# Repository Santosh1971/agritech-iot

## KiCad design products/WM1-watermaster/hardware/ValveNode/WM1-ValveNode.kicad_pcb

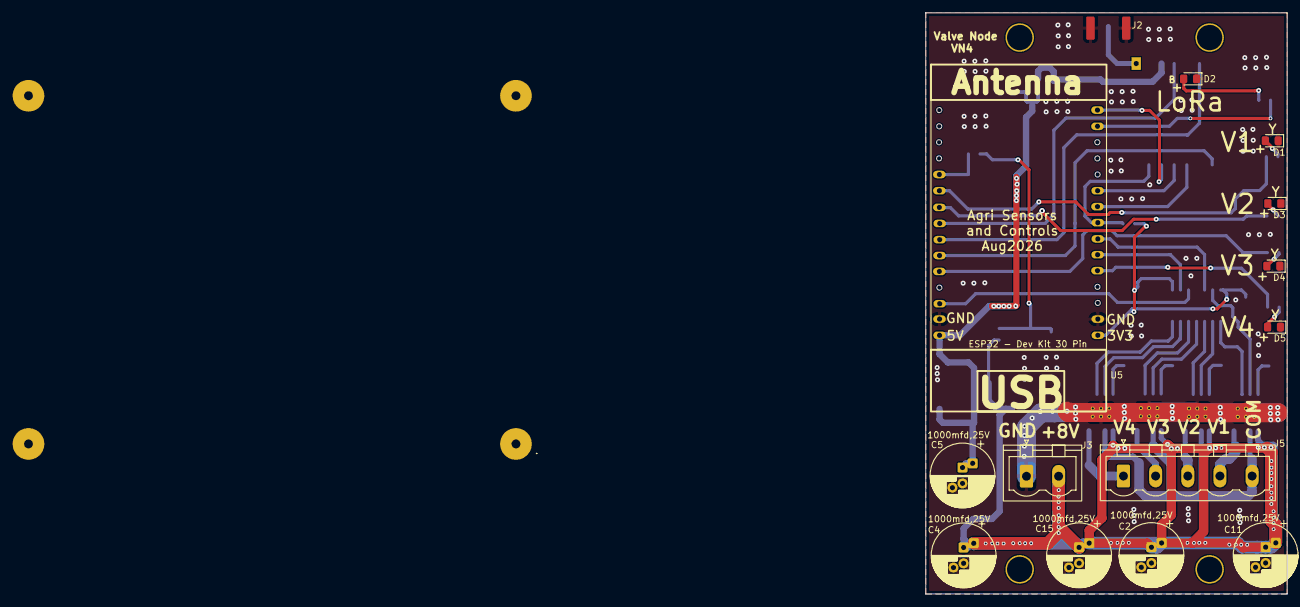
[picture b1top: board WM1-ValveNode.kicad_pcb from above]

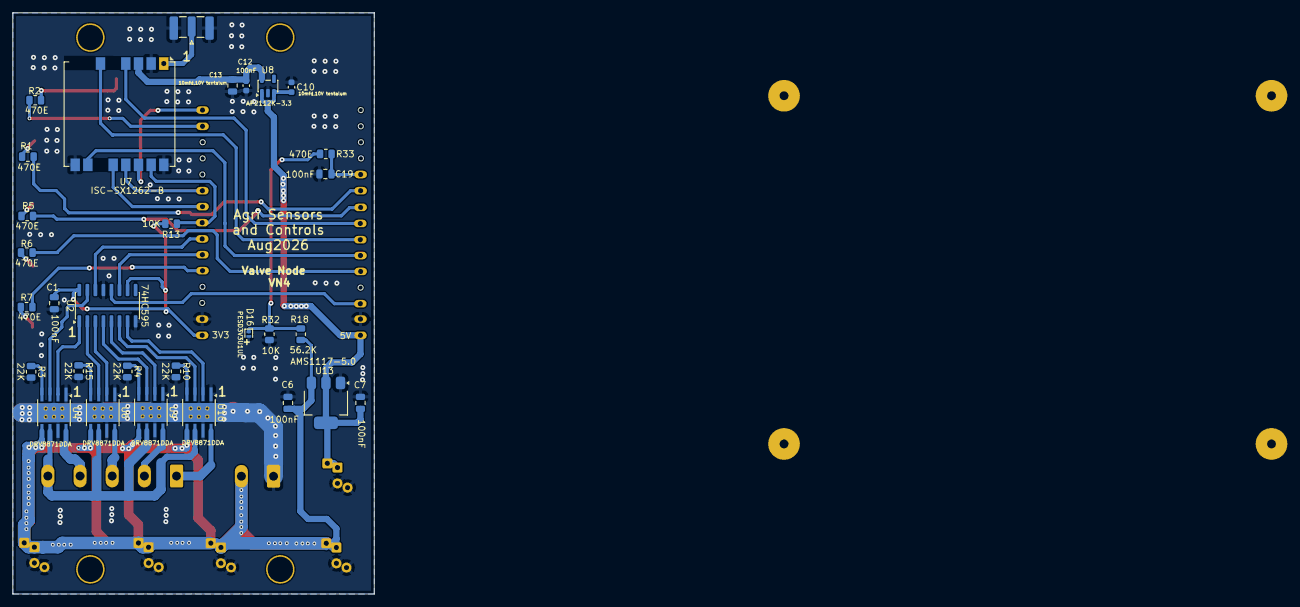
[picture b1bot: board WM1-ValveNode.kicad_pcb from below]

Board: 2 copper layers, 57.1 x 91.8 mm, 45 parts (30 on the bottom side), 45 nets.

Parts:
.: MountingHole; MountingHole_3.2mm_M3
C1, C6, C7, C13, C19: 100nF; C_0805_2012Metric
C2, C4, C5, C11, C15: 1000mfd,25V; CP_Radial_D10.0mm_P2.50mm_P5.00mm
C10, C12: 10mfd,10V tentalum; C_0603_1608Metric
D1: LED_V1_Yellow; LED_0805_2012Metric_Pad1.15x1.40mm_HandSolder
D2: LED_Blue_LoRa; LED_0805_2012Metric_Pad1.15x1.40mm_HandSolder
D3: LED_V2_Yellow; LED_0805_2012Metric_Pad1.15x1.40mm_HandSolder
D4: LED_V3_Yellow; LED_0805_2012Metric_Pad1.15x1.40mm_HandSolder
D5: LED_V4_Yellow; LED_0805_2012Metric_Pad1.15x1.40mm_HandSolder
D16: PESD3V3U1UL; D_SOD-882
H1: MountingHole; MountingHole_3.2mm_M3
J2: Conn_Coaxial_Small; SMA_Samtec_SMA-J-P-H-ST-EM1_EdgeMount
J3: PWR_CONN; PhoenixContact_MSTBVA_2,5_2-G-5,08_1x02_P5.08mm_Vertical
J5: Conn_01x05_Pin; PhoenixContact_MSTBVA_2,5_5-G-5,08_1x05_P5.08mm_Vertical
R1, R2, R5, R6, R7, R33: 470E; R_0805_2012Metric
R3, R4, R10, R15: 22K; R_0805_2012Metric
R13, R32: 10K; R_0805_2012Metric
R18: 56.2K; R_0805_2012Metric
U2: 74HC595; SOIC-16_3.9x9.9mm_P1.27mm
U4, U6, U9, U10: DRV8871DDA; Texas_HTSOP-8-1EP_3.9x4.9mm_P1.27mm_EP2.95x4.9mm_Mask2.4x3.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
U5: ESP32 30 Pin CP2102 Development Board; ESP32-C3-DevKitM-1
U7: ISC-SX1262-B; Ai-Thinker-Ra-01-LoRa
U8: AP2112K-3.3; SOT-23-5
U13: AMS1117-5.0; SOT-223-3_TabPin2

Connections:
+3.3V: C1.1, R13.1, U2.10 (~SRCLR), U2.16 (VCC), U5.1 (3V3_Out)
+3.3VL: C12.1, C13.1, U7.3 (VDD), U8.5 (VOUT)
+5V: C5.1, C7.1, C10.1, U5.30 (VIN/5V_Power_IN), U8.1 (VIN), U8.3 (EN), U13.2 (VO)
+8V: C2.1, C4.1, C6.1, C11.1, C15.1, J3.2, R18.1, U4.5 (VM), U6.5 (VM), U9.5 (VM), U10.5 (VM), U13.3 (VI)
/BUSY: U5.25 (D27), U7.10 (DIO4/BUSY)
/Batt_Mon: C19.1, R33.1, U5.20 (D35/Input_only)
/DIO1: U5.24 (D26), U7.6 (DIO1)
/LoRa_LED: R2.1, U5.14 (D22/I2C_SCL)
/MISO: U5.10 (D19), U7.13 (MISO)
/MOSI: U5.15 (D23), U7.14 (MOSI)
/NSS: R13.2, U5.8 (D5/BootSensitive), U7.15 (~NSS)
/RESET: U5.23 (D25), U7.4 (~RESET)
/SCK: U5.9 (D18), U7.12 (SCK)
/V1_IN1: U2.15 (QA), U4.3 (IN1)
/V1_IN2: U2.1 (QB), U4.2 (IN2)
/V1_LED: R1.1, U5.21 (D32)
/V1_OUT: J5.4, U4.8 (OUT2)
/V2_IN1: U2.2 (QC), U6.3 (IN1)
/V2_IN2: U2.3 (QD), U6.2 (IN2)
/V2_LED: R5.1, U5.22 (D33)
/V2_OUT: J5.3, U6.8 (OUT2)
/V3_IN1: U2.4 (QE), U9.3 (IN1)
/V3_IN2: U2.5 (QF), U9.2 (IN2)
/V3_LED: R6.1, U5.26 (D14)
/V3_OUT: J5.2, U9.8 (OUT2)
/V4_IN1: U2.6 (QG), U10.3 (IN1)
/V4_IN2: U2.7 (QH), U10.2 (IN2)
/V4_LED: R7.1, U5.5 (D4)
/V4_OUT: J5.1, U10.8 (OUT2)
/V_Com_OUT: J5.5, U4.6 (OUT1), U6.6 (OUT1), U9.6 (OUT1), U10.6 (OUT1)
/Valve_CLK: U2.11 (SRCLK), U5.6 (Rx2/D16)
/Valve_DATA: U2.14 (SER), U5.7 (Tx2/D17)
/Valve_LATCH: U2.12 (RCLK), U5.28 (D13)
GND: C1.2, C2.2, C4.2, C5.2, C6.2, C7.2, C10.2, C11.2, C12.2, C13.2, C15.2, C19.2, D1.1 (K), D2.1 (K), D3.1 (K), D4.1 (K), D5.1 (K), D16.2 (A), J2.2 (Ext), J3.1, R3.2, R4.2, R10.2, R15.2, R32.2, U2.8 (GND), U2.13 (~OE), U4.1 (GND), U4.7 (GND), U4.9 (GND), U5.2 (GND), U5.29 (GND), U6.1 (GND), U6.7 (GND), U6.9 (GND), U7.2 (GND), U7.9 (GND), U7.16 (GND), U8.2 (GND), U9.1 (GND), U9.7 (GND), U9.9 (GND), U10.1 (GND), U10.7 (GND), U10.9 (GND), U13.1 (GND)
unnamed: D1.2 (A), R1.2
unnamed: D2.2 (A), R2.2
unnamed: D3.2 (A), R5.2
unnamed: D4.2 (A), R6.2
unnamed: D5.2 (A), R7.2
unnamed: D16.1 (K), R18.2, R32.1, R33.2
unnamed: J2.1 (In), U7.1 (ANT)
unnamed: R3.1, U4.4 (ILIM)
unnamed: R15.1, U6.4 (ILIM)
unnamed: R4.1, U9.4 (ILIM)
unnamed: R10.1, U10.4 (ILIM)

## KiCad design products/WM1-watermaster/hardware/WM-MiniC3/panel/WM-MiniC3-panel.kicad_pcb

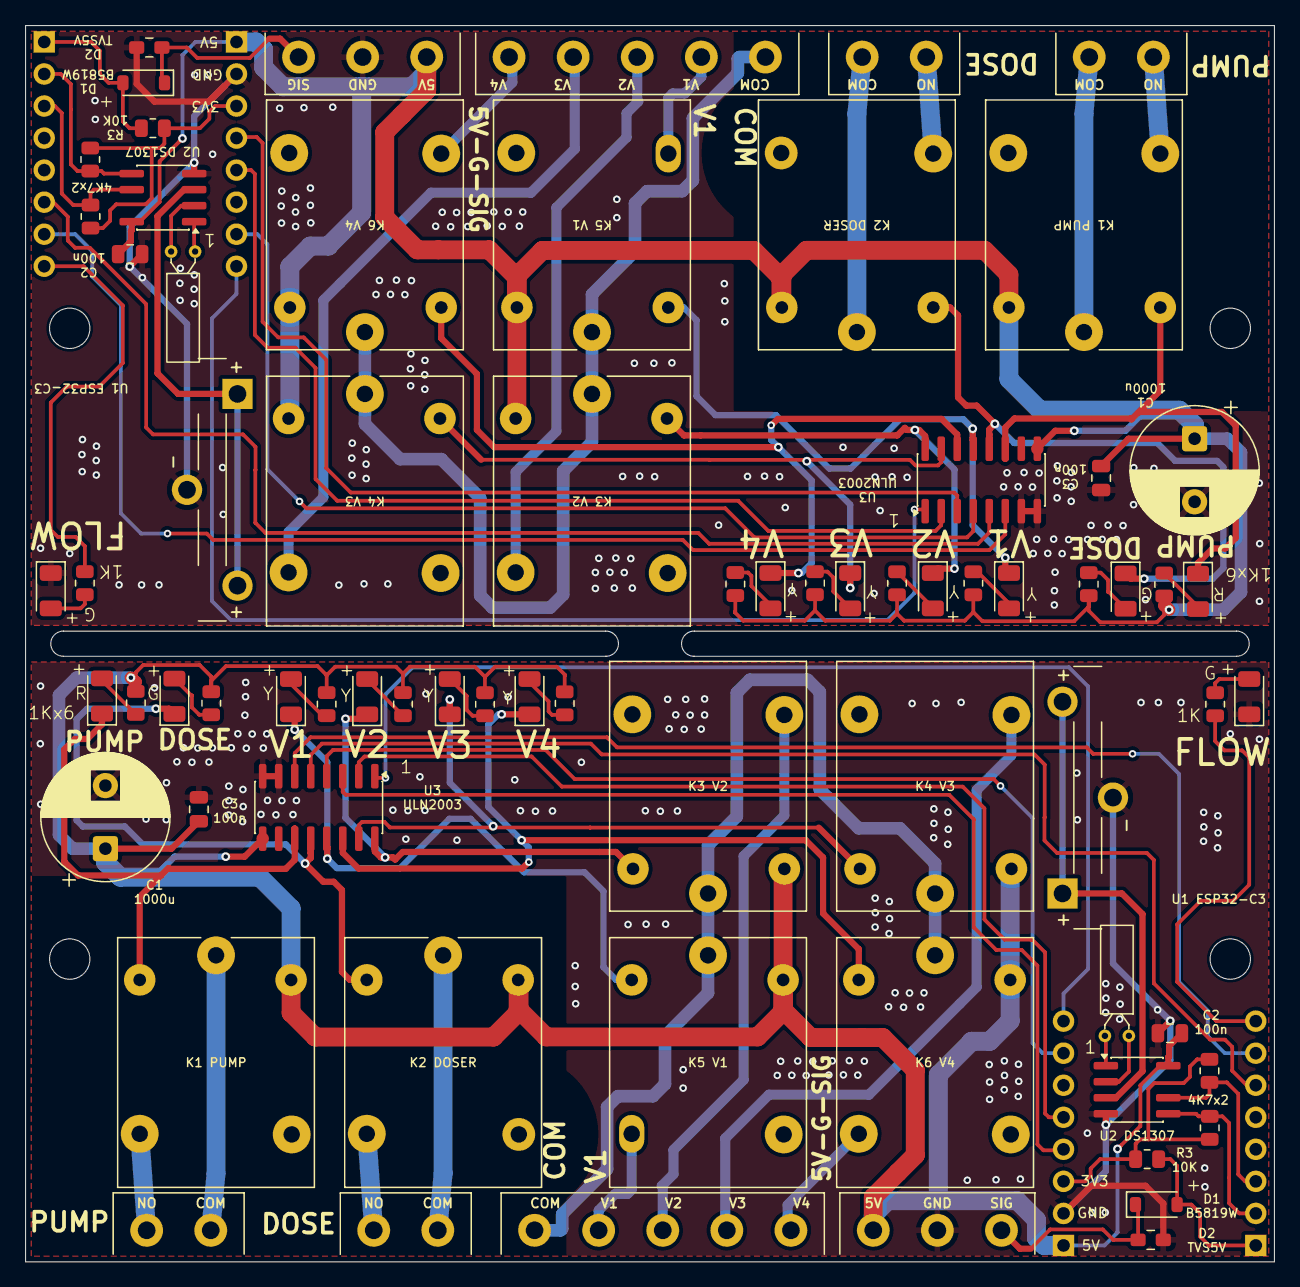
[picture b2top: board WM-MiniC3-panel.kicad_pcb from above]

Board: 2 copper layers, 99.0 x 98.0 mm, 78 parts (0 on the bottom side), 78 nets.

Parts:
BT1_1, BT1_2: CR2032; Battery_CR2032_Vertical_3pin
C1_1, C1_2: 1000u 16V; CP_Radial_D10.0mm_P5.00mm
C2_1, C2_2, C3_1, C3_2: 100n; C_0805_2012Metric
D1_1, D1_2: B5819W; D_SOD-123
D2_1, D2_2: SLCESDB5V0D5; D_SOD-523_HandSolder
D3_1, D3_2: GRN; LED_1206_3216Metric
D4_1, D4_2, D5_1, D5_2, D6_1, D6_2, D7_1, D7_2, D8_1, D8_2, D9_1, D9_2: YEL; LED_1206_3216Metric
H1_1, H1_2, H2_1, H2_2: M3; MountingHole_3.2mm_M3
J1_1, J1_2: FLOW; Pluggable_2EDGR_5.08_1x03_Horizontal
J2_1, J2_2: PUMP 230V; Pluggable_2EDGR_5.08_1x02_Horizontal
J3_1, J3_2: DOSER 230V; Pluggable_2EDGR_5.08_1x02_Horizontal
J4_1, J4_2: VALVES 24VAC; Pluggable_2EDGR_5.08_1x05_Horizontal
K1_1, K1_2, K2_1, K2_2, K3_1, K3_2, K4_1, K4_2, K5_1, K5_2, K6_1, K6_2: SRD-05VDC; Relay_SPDT_SANYOU_SRD_Outline
R1_1, R1_2, R2_1, R2_2: 4.7k; R_0805_2012Metric
R3_1, R3_2: 10k; R_0805_2012Metric
R4_1, R4_2, R6_1, R6_2, R7_1, R7_2, R8_1, R8_2, R9_1, R9_2, R10_1, R10_2, R11_1, R11_2: 1k; R_0805_2012Metric
U1_1, U1_2: ESP32-C3 Super Mini; ESP32-C3_SuperMini_Socket
U2_1, U2_2: DS1307Z+; SOIC-8_3.9x4.9mm_P1.27mm
U3_1, U3_2: ULN2003A; SOIC-16_3.9x9.9mm_P1.27mm
Y1_1, Y1_2: 32.768k; Crystal_C26-LF_D2.1mm_L6.5mm_Horizontal

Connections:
B1/+3V3: R1_1.1, R2_1.1, R3_1.1, U1_1.11 (3V3)
B1/+5V: C1_1.1, C2_1.1, C3_1.1, J1_1.1, K1_1.5, K2_1.5, K3_1.2, K4_1.2, K5_1.5, K6_1.5, R6_1.1, R7_1.1, R8_1.1, R9_1.1, R10_1.1, R11_1.1, U1_1.9 (5V), U2_1.8 (VCC), U3_1.9 (COM)
B1/COIL_DOSER: D4_1.1 (K), K2_1.2, U3_1.12 (O5)
B1/COIL_PUMP: D5_1.1 (K), K1_1.2, U3_1.11 (O6)
B1/COIL_V1: D6_1.1 (K), K5_1.2, U3_1.13 (O4)
B1/COIL_V2: D7_1.1 (K), K3_1.5, U3_1.16 (O1)
B1/COIL_V3: D8_1.1 (K), K4_1.5, U3_1.15 (O2)
B1/COIL_V4: D9_1.1 (K), K6_1.2, U3_1.14 (O3)
B1/DOSER_COM: J3_1.2, K2_1.1
B1/DOSER_NO: J3_1.1, K2_1.3
B1/FLOW: D1_1.2 (A), R3_1.2, U1_1.1 (IO5)
B1/FLOW_EXT: D1_1.1 (K), D2_1.1 (A1), J1_1.3
B1/GND: BT1_1.2 (-), C1_1.2, C2_1.2, C3_1.2, D2_1.2 (A2), D3_1.1 (K), J1_1.2, U1_1.10 (GND), U2_1.4 (GND), U3_1.7 (I7), U3_1.8 (GND)
B1/LED_FLOW: R4_1.1, U1_1.8 (IO21)
B1/Net-(D3-A): D3_1.2 (A), R4_1.2
B1/Net-(D4-A): D4_1.2 (A), R6_1.2
B1/Net-(D5-A): D5_1.2 (A), R7_1.2
B1/Net-(D6-A): D6_1.2 (A), R8_1.2
B1/Net-(D7-A): D7_1.2 (A), R9_1.2
B1/Net-(D8-A): D8_1.2 (A), R10_1.2
B1/Net-(D9-A): D9_1.2 (A), R11_1.2
B1/PUMP_COM: J2_1.2, K1_1.1
B1/PUMP_NO: J2_1.1, K1_1.3
B1/RLY_DOSER: U1_1.6 (IO10), U3_1.5 (I5)
B1/RLY_PUMP: U1_1.7 (IO20), U3_1.6 (I6)
B1/RLY_V1: U1_1.15 (IO1), U3_1.4 (I4)
B1/RLY_V2: U1_1.16 (IO0), U3_1.1 (I1)
B1/RLY_V3: U1_1.13 (IO3), U3_1.2 (I2)
B1/RLY_V4: U1_1.12 (IO4), U3_1.3 (I3)
B1/SCL: R2_1.2, U1_1.3 (IO7), U2_1.6 (SCL)
B1/SDA: R1_1.2, U1_1.2 (IO6), U2_1.5 (SDA)
B1/V1_NO: J4_1.2, K5_1.3
B1/V2_NO: J4_1.3, K3_1.3
B1/V3_NO: J4_1.4, K4_1.3
B1/V4_NO: J4_1.5, K6_1.3
B1/VALVE_COM: J4_1.1, K3_1.1, K4_1.1, K5_1.1, K6_1.1
B1/VBAT: BT1_1.1 (+), U2_1.3 (VBAT)
B1/XT1: U2_1.1 (X1), Y1_1.2
B1/XT2: U2_1.2 (X2), Y1_1.1
B2/+3V3: R1_2.1, R2_2.1, R3_2.1, U1_2.11 (3V3)
B2/+5V: C1_2.1, C2_2.1, C3_2.1, J1_2.1, K1_2.5, K2_2.5, K3_2.2, K4_2.2, K5_2.5, K6_2.5, R6_2.1, R7_2.1, R8_2.1, R9_2.1, R10_2.1, R11_2.1, U1_2.9 (5V), U2_2.8 (VCC), U3_2.9 (COM)
B2/COIL_DOSER: D4_2.1 (K), K2_2.2, U3_2.12 (O5)
B2/COIL_PUMP: D5_2.1 (K), K1_2.2, U3_2.11 (O6)
B2/COIL_V1: D6_2.1 (K), K5_2.2, U3_2.13 (O4)
B2/COIL_V2: D7_2.1 (K), K3_2.5, U3_2.16 (O1)
B2/COIL_V3: D8_2.1 (K), K4_2.5, U3_2.15 (O2)
B2/COIL_V4: D9_2.1 (K), K6_2.2, U3_2.14 (O3)
B2/DOSER_COM: J3_2.2, K2_2.1
B2/DOSER_NO: J3_2.1, K2_2.3
B2/FLOW: D1_2.2 (A), R3_2.2, U1_2.1 (IO5)
B2/FLOW_EXT: D1_2.1 (K), D2_2.1 (A1), J1_2.3
B2/GND: BT1_2.2 (-), C1_2.2, C2_2.2, C3_2.2, D2_2.2 (A2), D3_2.1 (K), J1_2.2, U1_2.10 (GND), U2_2.4 (GND), U3_2.7 (I7), U3_2.8 (GND)
B2/LED_FLOW: R4_2.1, U1_2.8 (IO21)
B2/Net-(D3-A): D3_2.2 (A), R4_2.2
B2/Net-(D4-A): D4_2.2 (A), R6_2.2
B2/Net-(D5-A): D5_2.2 (A), R7_2.2
B2/Net-(D6-A): D6_2.2 (A), R8_2.2
B2/Net-(D7-A): D7_2.2 (A), R9_2.2
B2/Net-(D8-A): D8_2.2 (A), R10_2.2
B2/Net-(D9-A): D9_2.2 (A), R11_2.2
B2/PUMP_COM: J2_2.2, K1_2.1
B2/PUMP_NO: J2_2.1, K1_2.3
B2/RLY_DOSER: U1_2.6 (IO10), U3_2.5 (I5)
B2/RLY_PUMP: U1_2.7 (IO20), U3_2.6 (I6)
B2/RLY_V1: U1_2.15 (IO1), U3_2.4 (I4)
B2/RLY_V2: U1_2.16 (IO0), U3_2.1 (I1)
B2/RLY_V3: U1_2.13 (IO3), U3_2.2 (I2)
B2/RLY_V4: U1_2.12 (IO4), U3_2.3 (I3)
B2/SCL: R2_2.2, U1_2.3 (IO7), U2_2.6 (SCL)
B2/SDA: R1_2.2, U1_2.2 (IO6), U2_2.5 (SDA)
B2/V1_NO: J4_2.2, K5_2.3
B2/V2_NO: J4_2.3, K3_2.3
B2/V3_NO: J4_2.4, K4_2.3
B2/V4_NO: J4_2.5, K6_2.3
B2/VALVE_COM: J4_2.1, K3_2.1, K4_2.1, K5_2.1, K6_2.1
B2/VBAT: BT1_2.1 (+), U2_2.3 (VBAT)
B2/XT1: U2_2.1 (X1), Y1_2.2
B2/XT2: U2_2.2 (X2), Y1_2.1

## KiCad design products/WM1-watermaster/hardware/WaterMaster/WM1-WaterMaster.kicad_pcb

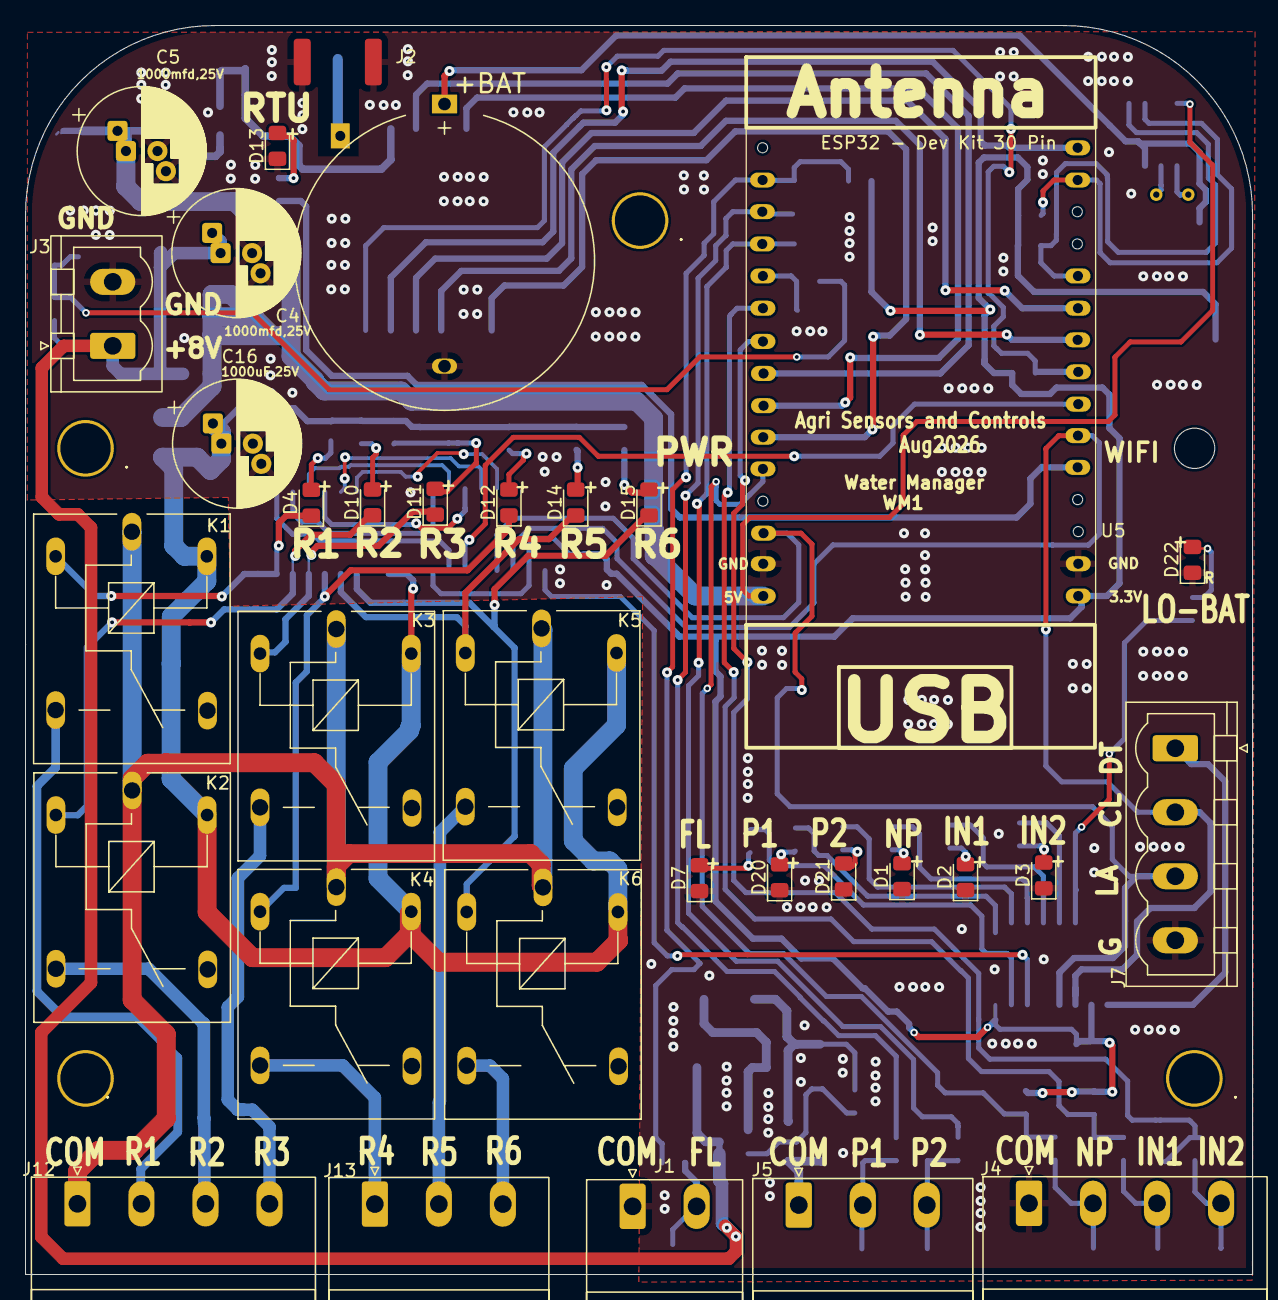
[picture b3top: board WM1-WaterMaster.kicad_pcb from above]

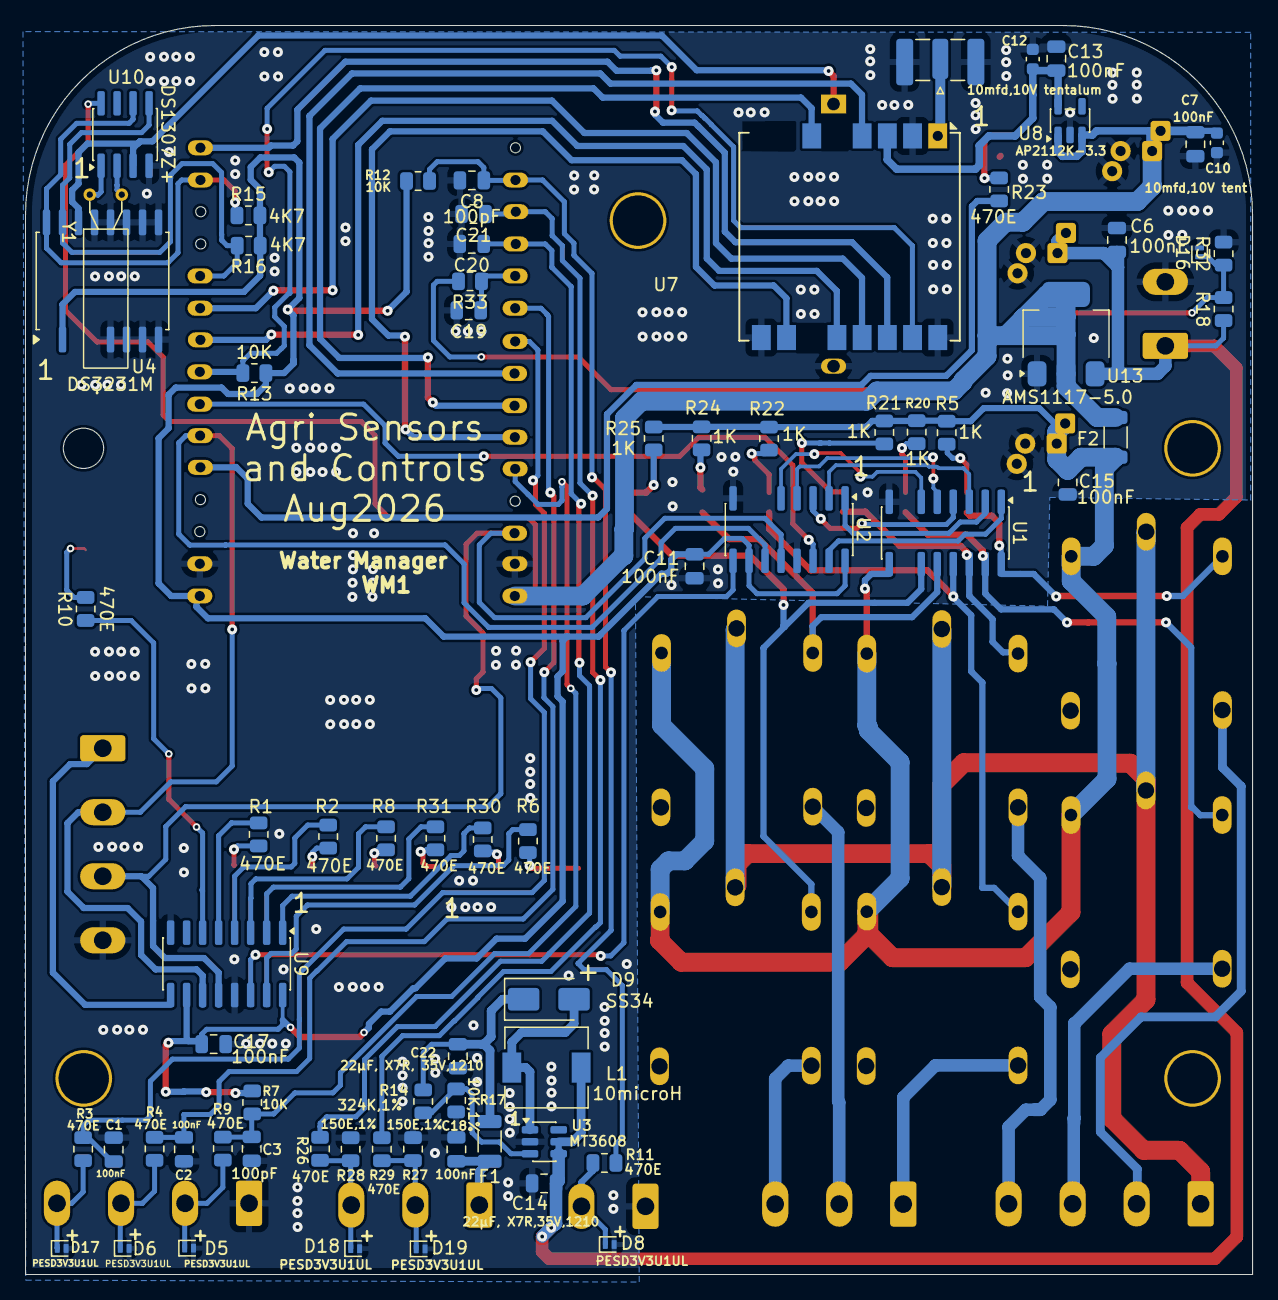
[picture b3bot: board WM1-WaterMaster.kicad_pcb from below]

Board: 2 copper layers, 97.4 x 99.1 mm, 109 parts (73 on the bottom side), 83 nets.

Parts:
., .#2, .#3, .#4, .#5: MountingHole; MountingHole_3.2mm_M3
BT1: CR2032; BatteryHolder_MYOUNG_BS-07-A1BJ001_CR2032
C1, C2, C6, C7, C11, C13, C15, C17, C18, C19: 100nF; C_0805_2012Metric
C3, C8, C20, C21: 100pF; C_0805_2012Metric
C4, C5: 1000mfd,25V; CP_Radial_D10.0mm_P2.50mm_P5.00mm
C10: 10mfd,10V tent; C_0603_1608Metric
C12: 10mfd,10V tentalum; C_0603_1608Metric
C14: 22µF, X7R,35V,1210; C_0805_2012Metric
C16: 1000uF,25V; CP_Radial_D10.0mm_P2.50mm_P5.00mm
C22: 22µF, X7R, 35V,1210; C_0805_2012Metric
D1: LED_GREEN_IN1; LED_0805_2012Metric_Pad1.15x1.40mm_HandSolder
D2: LED_GREEN_IN2; LED_0805_2012Metric_Pad1.15x1.40mm_HandSolder
D3: LED_GREEN_IN3; LED_0805_2012Metric_Pad1.15x1.40mm_HandSolder
D4, D10, D11, D12, D14, D15: LED_YELLOW_PUMP; LED_0805_2012Metric_Pad1.15x1.40mm_HandSolder
D5, D6, D8, D16, D17, D18, D19: PESD3V3U1UL; D_SOD-882
D7: LED_Green_Flow; LED_0805_2012Metric_Pad1.15x1.40mm_HandSolder
D9: SS34; D_SMA
D13: LED_Yellow_LoRa; LED_0805_2012Metric_Pad1.15x1.40mm_HandSolder
D20: LED_Green_PR1; LED_0805_2012Metric_Pad1.15x1.40mm_HandSolder
D21: LED_Green_PR2; LED_0805_2012Metric_Pad1.15x1.40mm_HandSolder
D22: LED_R_LoBAT; LED_0805_2012Metric_Pad1.15x1.40mm_HandSolder
F1, F2: Polyfuse_Small; L_1206_3216Metric
J1: Flow_CONN; PhoenixContact_MSTBA_2,5_2-G-5,08_1x02_P5.08mm_Horizontal
J2: Conn_Coaxial_Small; SMA_Samtec_SMA-J-P-H-ST-EM1_EdgeMount
J3: PWR_CONN; PhoenixContact_MSTBVA_2,5_2-G-5,08_1x02_P5.08mm_Vertical
J4: Conn_IN; PhoenixContact_MSTBA_2,5_4-G-5,08_1x04_P5.08mm_Horizontal
J5, J13: Conn_01x03_Pin; PhoenixContact_MSTBA_2,5_3-G-5,08_1x03_P5.08mm_Horizontal
J7: Conn_RLY_EXTENDER; PhoenixContact_MSTBVA_2,5_4-G-5,08_1x04_P5.08mm_Vertical
J12: Conn_01x04_Pin; PhoenixContact_MSTBA_2,5_4-G-5,08_1x04_P5.08mm_Horizontal
K1, K2, K3, K4, K5, K6: Cube_Relay; Relay_SPDT_SANYOU_SRD_Series_Form_C
L1: 10microH; L_6.3x6.3_H3
R1, R2, R3, R4, R6, R8, R9, R10, R11, R23, R28, R29, R30, R31, R33: 470E; R_0805_2012Metric
R5, R20, R21, R22, R24, R25: 1K; R_0805_2012Metric
R7, R12, R13, R32: 10K; R_0805_2012Metric
R14: 324K,1%; R_0805_2012Metric
R15, R16: 4K7; R_0805_2012Metric
R17: 10K,1%; R_0805_2012Metric
R18: 56.2K; R_0805_2012Metric
R26, R27: 150E,1%; R_0805_2012Metric
U1: ULN2003; SOIC-16_3.9x9.9mm_P1.27mm
U2, U9: 74HC595; SOIC-16_3.9x9.9mm_P1.27mm
U3: MT3608; SOT-23-6
U4: DS3231M; SOIC-16W_7.5x10.3mm_P1.27mm
U5: ESP32 30 Pin CP2102 Development Board; ESP32-C3-DevKitM-1
U7: ISC-SX1262-B; Ai-Thinker-Ra-01-LoRa
U8: AP2112K-3.3; SOT-23-5
U10: DS1307Z+; SOIC-8_3.9x4.9mm_P1.27mm
U13: AMS1117-5.0; SOT-223-3_TabPin2
Y1: Crystal; Crystal_AT310_D3.0mm_L10.0mm_Horizontal

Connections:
+3.3V: C11.1, C17.1, R7.1, R12.1, R13.1, R15.1, R16.1, U2.10 (~SRCLR), U2.16 (VCC), U4.2 (VCC), U5.1 (3V3_Out), U9.10 (~SRCLR), U9.16 (VCC)
+3.3VL: C12.1, C13.1, U7.3 (VDD), U8.5 (VOUT)
+5V: C5.1, C7.1, C10.1, F2.1, U5.30 (VIN/5V_Power_IN), U8.1 (VIN), U8.3 (EN), U10.8 (VCC), U13.2 (VO)
+5VR: C15.1, C16.1, F2.2, K1.5, K2.5, K3.5, K4.5, K5.5, K6.5, R5.1, R20.1, R21.1, R22.1, R24.1, R25.1, U1.9 (COM)
+8V: C4.1, C6.1, C14.1, J3.1, L1.1, R18.1, U3.4 (EN), U3.5 (IN), U13.3 (VI)
+20V: C22.1, D9.1 (K), F1.1, R14.1
+20VPR: C18.1, F1.2, J5.1
/BATT: BT1.1 (+), U4.14 (VBAT), U10.3 (VBAT)
/BUSY: U5.25 (D27), U7.10 (DIO4/BUSY)
/Batt_Mon: C19.1, R33.1, U5.20 (D35/Input_only)
/DIO1: U5.24 (D26), U7.6 (DIO1)
/Flow_CON: D8.1 (K), J1.2, R11.2
/Flow_LED: R6.1, U9.15 (QA)
/Flow_MCU: C8.1, R11.1, R12.2, U5.17 (VP(36)/Input_only)
/IN1: C3.1, R7.2, R9.1, U5.26 (D14)
/IN1_CON: D5.1 (K), J4.2, R9.2
/IN1_LED: R8.1, U9.3 (QD)
/IN2: C2.1, R4.1, U5.21 (D32)
/IN2_CON: D6.1 (K), J4.3, R4.2
/IN2_LED: R2.1, U9.4 (QE)
/IN3: C1.1, R3.1, U5.22 (D33)
/IN3_CON: D17.1 (K), J4.4, R3.2
/IN3_LED: R1.1, U9.5 (QF)
/LOBATT_LED: R10.1, U9.6 (QG)
/LoRa_LED: R23.1, U5.5 (D4)
/MISO: U5.10 (D19), U7.13 (MISO)
/MOSI: U5.15 (D23), U7.14 (MOSI)
/NSS: R13.2, U5.8 (D5/BootSensitive), U7.15 (~NSS)
/PR1_LED: R30.1, U9.1 (QB)
/PR2_LED: R31.1, U9.2 (QC)
/Press_IN1_CON: D19.1 (K), J5.2, R27.1, R29.2
/Press_IN1_MCU: C21.1, R29.1, U5.18 (VN(39)/Input_only)
/Press_IN2_CON: D18.1 (K), J5.3, R26.1, R28.2
/Press_IN2_MCU: C20.1, R28.1, U5.19 (D34/Input_only)
/RELAY1_COIL: D4.1 (K), K1.2, U1.16 (O1)
/RELAY1_MCU: U1.1 (I1), U2.15 (QA)
/RELAY2_COIL: D10.1 (K), K2.2, U1.15 (O2)
/RELAY2_MCU: U1.2 (I2), U2.1 (QB)
/RELAY3_COIL: D11.1 (K), K3.2, U1.14 (O3)
/RELAY3_MCU: U1.3 (I3), U2.2 (QC)
/RELAY4_COIL: D12.1 (K), K4.2, U1.13 (O4)
/RELAY4_MCU: U1.4 (I4), U2.3 (QD)
/RELAY5_COIL: D14.1 (K), K5.2, U1.12 (O5)
/RELAY5_MCU: U1.5 (I5), U2.4 (QE)
/RELAY6_COIL: D15.1 (K), K6.2, U1.11 (O6)
/RELAY6_MCU: U1.6 (I6), U2.5 (QF)
/RESET: U5.23 (D25), U7.4 (~RESET)
/RLY1_CON_1: J12.2, K1.3
/RLY2_CON_1: J12.3, K2.3
/RLY3_CON_1: J12.4, K3.3
/RLY4_CON_1: J13.1, K4.3
/RLY5_CON_1: J13.2, K5.3
/RLY6_CON_1: J13.3, K6.3
/RLY_CLK: J7.2, U2.11 (SRCLK), U5.6 (Rx2/D16), U9.11 (SRCLK)
/RLY_COMM: J12.1, K1.1, K2.1, K3.1, K4.1, K5.1, K6.1
/RLY_DATA: U2.14 (SER), U5.7 (Tx2/D17)
/RLY_DATA_EXT: J7.1, U9.9 (QH')
/RLY_DATA_OUT: U2.9 (QH'), U9.14 (SER)
/RLY_LATCH: J7.3, U2.12 (RCLK), U5.28 (D13), U9.12 (RCLK)
/SCK: U5.9 (D18), U7.12 (SCK)
/SCL: R15.2, U4.16 (SCL), U5.14 (D22/I2C_SCL), U10.6 (SCL)
/SDA: R16.2, U4.15 (SDA), U5.11 (D21/I2C_SDA), U10.5 (SDA)
GND: BT1.2 (-), C1.2, C2.2, C3.2, C4.2, C5.2, C6.2, C7.2, C8.2, C10.2, C11.2, C12.2, C13.2, C14.2, C15.2, C16.2, C17.2, C18.2, C19.2, C20.2, C21.2, C22.2, D1.1 (K), D2.1 (K), D3.1 (K), D5.2 (A), D6.2 (A), D7.1 (K), D8.2 (A), D13.1 (K), D16.2 (A), D17.2 (A), D18.2 (A), D19.2 (A), D20.1 (K), D21.1 (K), D22.1 (K), J1.1, J2.2 (Ext), J3.2, J4.1, J7.4, R17.2, R26.2, R27.2, R32.2, U1.8 (GND), U2.8 (GND), U2.13 (~OE), U3.2 (GND), U4.5 (GND), U4.6 (GND), U4.7 (GND), U4.8 (GND), U4.9 (GND), U4.10 (GND), U4.11 (GND), U4.12 (GND), U4.13 (GND), U5.2 (GND), U5.29 (GND), U7.2 (GND), U7.9 (GND), U7.16 (GND), U8.2 (GND), U9.8 (GND), U9.13 (~OE), U10.4 (GND), U13.1 (GND)
unnamed: D1.2 (A), R8.2
unnamed: D2.2 (A), R2.2
unnamed: D3.2 (A), R1.2
unnamed: D4.2 (A), R5.2
unnamed: D7.2 (A), R6.2
unnamed: D9.2 (A), L1.2, U3.1 (SW)
unnamed: D10.2 (A), R20.2
unnamed: D11.2 (A), R21.2
unnamed: D12.2 (A), R22.2
unnamed: D13.2 (A), R23.2
unnamed: D14.2 (A), R24.2
unnamed: D15.2 (A), R25.2
unnamed: D16.1 (K), R18.2, R32.1, R33.2
unnamed: D20.2 (A), R30.2
unnamed: D21.2 (A), R31.2
unnamed: D22.2 (A), R10.2
unnamed: J2.1 (In), U7.1 (ANT)
unnamed: R14.2, R17.1, U3.3 (FB)
unnamed: U10.1 (X1), Y1.1
unnamed: U10.2 (X2), Y1.2
